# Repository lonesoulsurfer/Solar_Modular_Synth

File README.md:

# Solar Modular Synth
 A modular synth based around Arduino
First and foremost - a big shoutout to the creative team over at [Bleep Labs](https://bleeplabs.com/) for the original build which is called the Neblophone.

I wanted to be able to add some playability to the little modular synth that I'm putting together and after a extensive search on Google I stumbled on the Neblophone which I have re-named 'Solar' for this build.

The main changes that I have implemented are; I changed the stylus style keyboard over to actual momentary switches, I designed a front panel and custom PCB which can be used in Eurorack modules (or as a fun standalone synth) and lastly, added 2 sync inputs so you can connect it to other synths.

The sync inputs can be a little fiddily but once tuned in work great.  However, you don;t have to sync in the synth as you can just play it over the top of whatever you are jamming to.

So what are the features of the little synth?

– Eight waveforms

– Light controlled (Vactrol) analog low-pass filter with five adjustable LFO LED modes.

– Perfect tuning across six octaves.

– Adjustable temperament and key.

– Six arpeggio modes with adjustable rate.

The main goal with building this module is to create my own 'simple to build' modular synth. I wanted to keep everything as easy as possble with each module built with the following aims:

-   Can be powered by 9V (and 12V)

-   Easy to build with minimum components

-   Use Arduino to keep it simple (plus it helps to keep the components down and everything in tune)

-   Can fit into any modular synth Eurorck (include the ability to power the module via normal module power sources)

-   Has to sound great!

It's the first time that I have utilized cherry MX switches and I'm so glad that I used them! 
Lastly, as I have mentioned above, Solar makes a fun standalone synth and has been designed to be able to fit in Eurorack modules and powered via a Eurorack power supply!

I have also completed a step by step guide which you can find on Instructables

YouTube vid can be found below
https://www.youtube.com/watch?v=ggaYos6u02A

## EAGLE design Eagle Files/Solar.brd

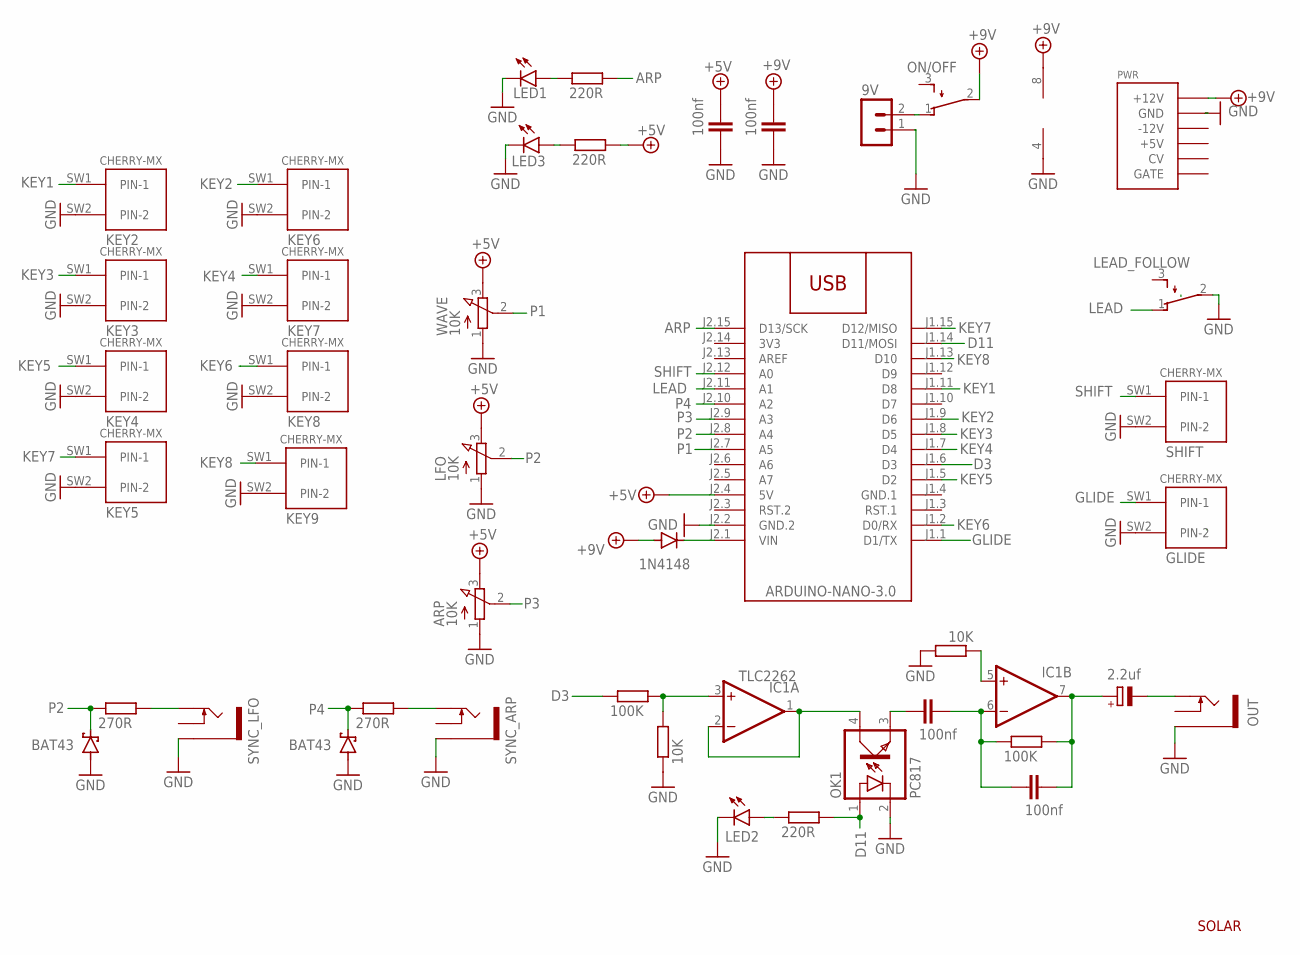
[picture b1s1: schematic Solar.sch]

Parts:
9V: B2B-PH-K-S
ARP: 10K; EVUFXL
C1, C2, C3, C5: 100nf; C050-024X044
C4: 2.2uf; E2,5-6E
D1, D3: BAT43; DO35-10
D2: 1N4148; DO35-7
GLIDE: CHERRY-MX
IC1: TLC2262; DIL08
KEY2, KEY3, KEY4, KEY5, KEY6, KEY7, KEY8, KEY9: CHERRY-MX
LEAD_FOLLOW: TL32PO; TL3XPO
LED1, LED2: LED3MM
LED3: LED5MM
LFO: 10K; EVUFXL
M1: ARDUINO-NANO-3.0
OK1: PC817; DIL04
ON/OFF: TL32PO; TL3XPO
OUT: THONKICONNNEW; WQP-PJ301M-12_JACK
PWR: POWER; POWER_16
R1, R3: 100K; 0207/10
R2, R4: 10K; 0207/10
R5, R8, R10: 220R; 0207/10
R6, R7: 270R; 0207/10
SHIFT: CHERRY-MX
SYNC_ARP: THONKICONNNEW; WQP-PJ301M-12_JACK
SYNC_LFO: THONKICONNNEW; WQP-PJ301M-12_JACK
WAVE: 10K; EVUFXL

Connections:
3V3: M1.J2.14 (3V3)
+5V: ARP.3 (E), C5.2, LFO.3 (E), M1.J2.4 (5V), R5.2, WAVE.3 (E)
+9V: C2.2, D2.A, IC1.8 (V+), ON/OFF.2, PWR.9 (+12V), PWR.10 (+12V)
ARP: M1.J2.15 (D13/SCK), R8.2
D3: M1.J1.6 (D3), R1.1
D11: M1.J1.14 (D11/MOSI), OK1.1 (A), R10.2
GLIDE: GLIDE.SW1 (PIN-1), M1.J1.1 (D1/TX)
GND: 9V.1, ARP.1 (A), C2.1, C5.1, D1.A, D3.A, GLIDE.SW2 (PIN-2), IC1.4 (V-), KEY2.SW2 (PIN-2), KEY3.SW2 (PIN-2), KEY4.SW2 (PIN-2), KEY5.SW2 (PIN-2), KEY6.SW2 (PIN-2), KEY7.SW2 (PIN-2), KEY8.SW2 (PIN-2), KEY9.SW2 (PIN-2), LEAD_FOLLOW.2, LED1.K (C), LED2.K (C), LED3.K (C), LFO.1 (A), M1.J2.2 (GND.2), OK1.2 (C), OUT.P$3_SLEEVE (SLEEVE), PWR.3 (GND), PWR.4 (GND), PWR.5 (GND), PWR.6 (GND), PWR.7 (GND), PWR.8 (GND), R2.1, R4.2, SHIFT.SW2 (PIN-2), SYNC_ARP.P$3_SLEEVE (SLEEVE), SYNC_LFO.P$3_SLEEVE (SLEEVE), WAVE.1 (A)
GND.1: M1.J1.4 (GND.1)
KEY1: KEY2.SW1 (PIN-1), M1.J1.11 (D8)
KEY2: KEY6.SW1 (PIN-1), M1.J1.9 (D6)
KEY3: KEY3.SW1 (PIN-1), M1.J1.8 (D5)
KEY4: KEY7.SW1 (PIN-1), M1.J1.7 (D4)
KEY5: KEY4.SW1 (PIN-1), M1.J1.5 (D2)
KEY6: KEY8.SW1 (PIN-1), M1.J1.2 (D0/RX)
KEY7: KEY5.SW1 (PIN-1), M1.J1.15 (D12/MISO)
KEY8: KEY9.SW1 (PIN-1), M1.J1.13 (D10)
LEAD: LEAD_FOLLOW.1 (O), M1.J2.11 (A1)
unnamed: LED1.A, R8.1
unnamed: 9V.2, ON/OFF.1 (O)
unnamed: IC1.3 (+IN), R1.2, R2.2
unnamed: R7.2, SYNC_LFO.P$1_TIP (TIP)
unnamed: IC1.1 (OUT), IC1.2 (-IN), OK1.4 (COL)
unnamed: C1.1, OK1.3 (EMIT)
unnamed: C1.2, C3.1, IC1.6 (-IN), R3.1
unnamed: IC1.5 (+IN), R4.1
unnamed: C3.2, C4.+, IC1.7 (OUT), R3.2
unnamed: C4.-, OUT.P$1_TIP (TIP)
unnamed: LED3.A, R5.1
unnamed: R6.2, SYNC_ARP.P$1_TIP (TIP)
unnamed: LED2.A, R10.1
unnamed: D2.C, M1.J2.1 (VIN)
P1: M1.J2.7 (A5), WAVE.2 (S)
P2: D1.C, LFO.2 (S), M1.J2.8 (A4), R7.1
P3: ARP.2 (S), M1.J2.9 (A3)
P4: D3.C, M1.J2.10 (A2), R6.1
SHIFT: M1.J2.12 (A0), SHIFT.SW1 (PIN-1)

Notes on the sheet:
SOLAR

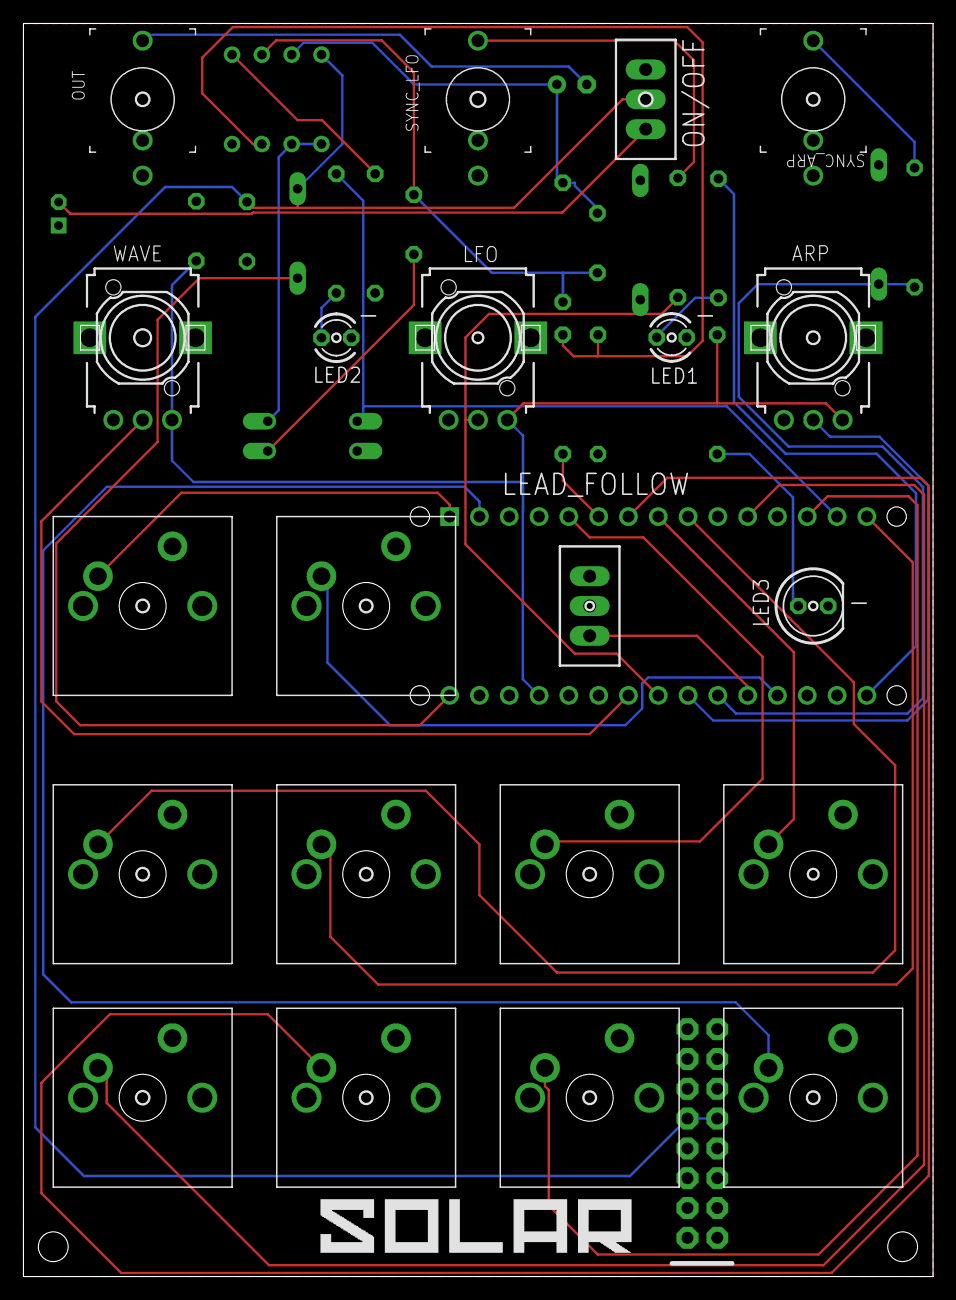
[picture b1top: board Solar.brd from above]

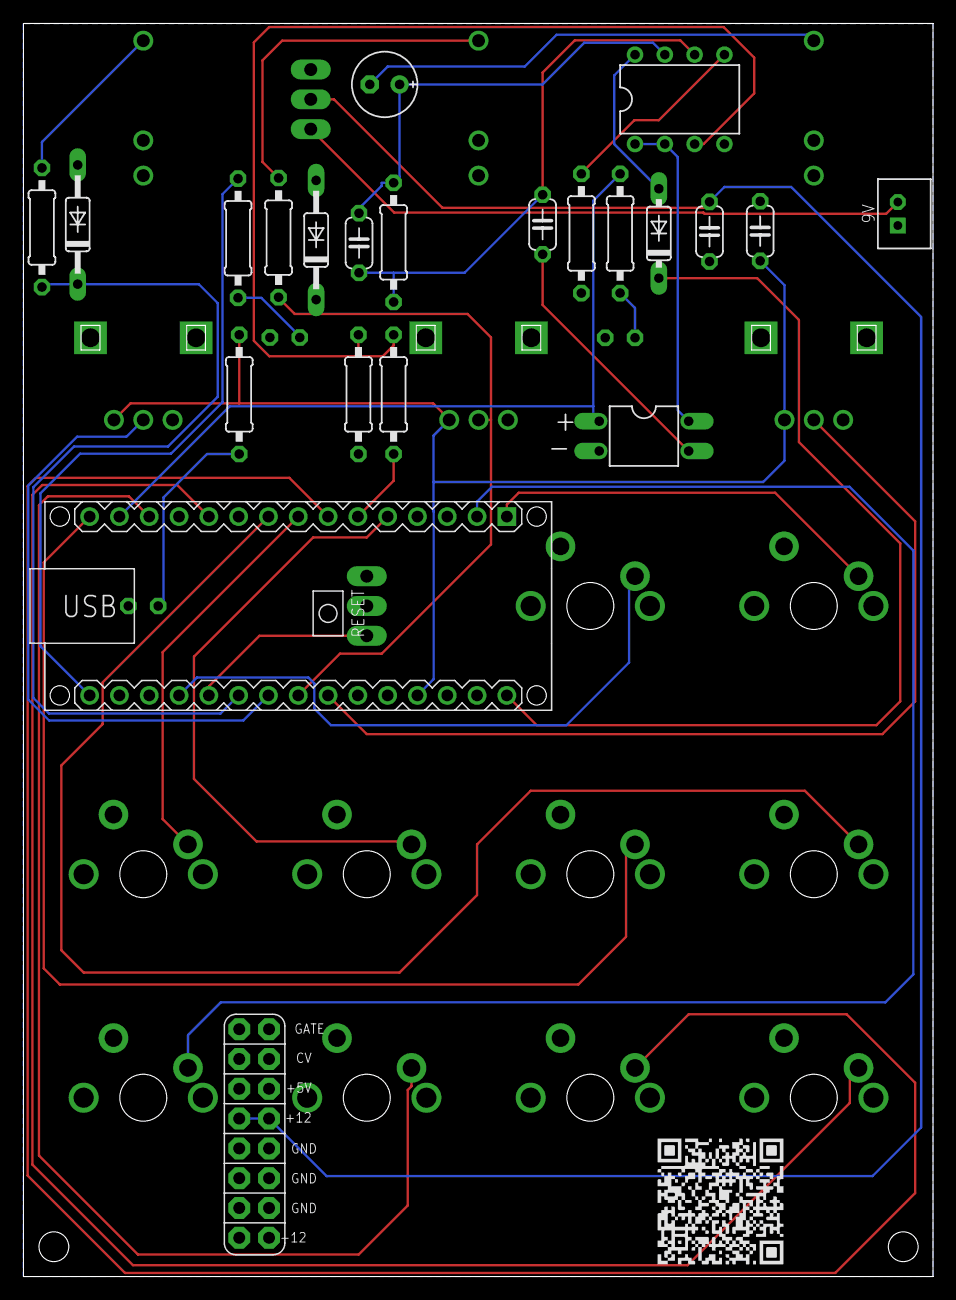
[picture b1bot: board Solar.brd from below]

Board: 2 copper layers, 77.5 x 106.8 mm, 43 parts (22 on the bottom side), 35 nets.

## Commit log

2025-02-18 files
2025-02-18 updated names
2025-02-20 Create Solar - Parts List.pdf
    added parts list
2025-03-01 file updates
2025-03-02 Updated front panel

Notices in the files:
parts and their libraries:
diy-modules: Released under the Creative Commons Attribution 4.0 International License: http://creativecommons.org/licenses/by/4.0
